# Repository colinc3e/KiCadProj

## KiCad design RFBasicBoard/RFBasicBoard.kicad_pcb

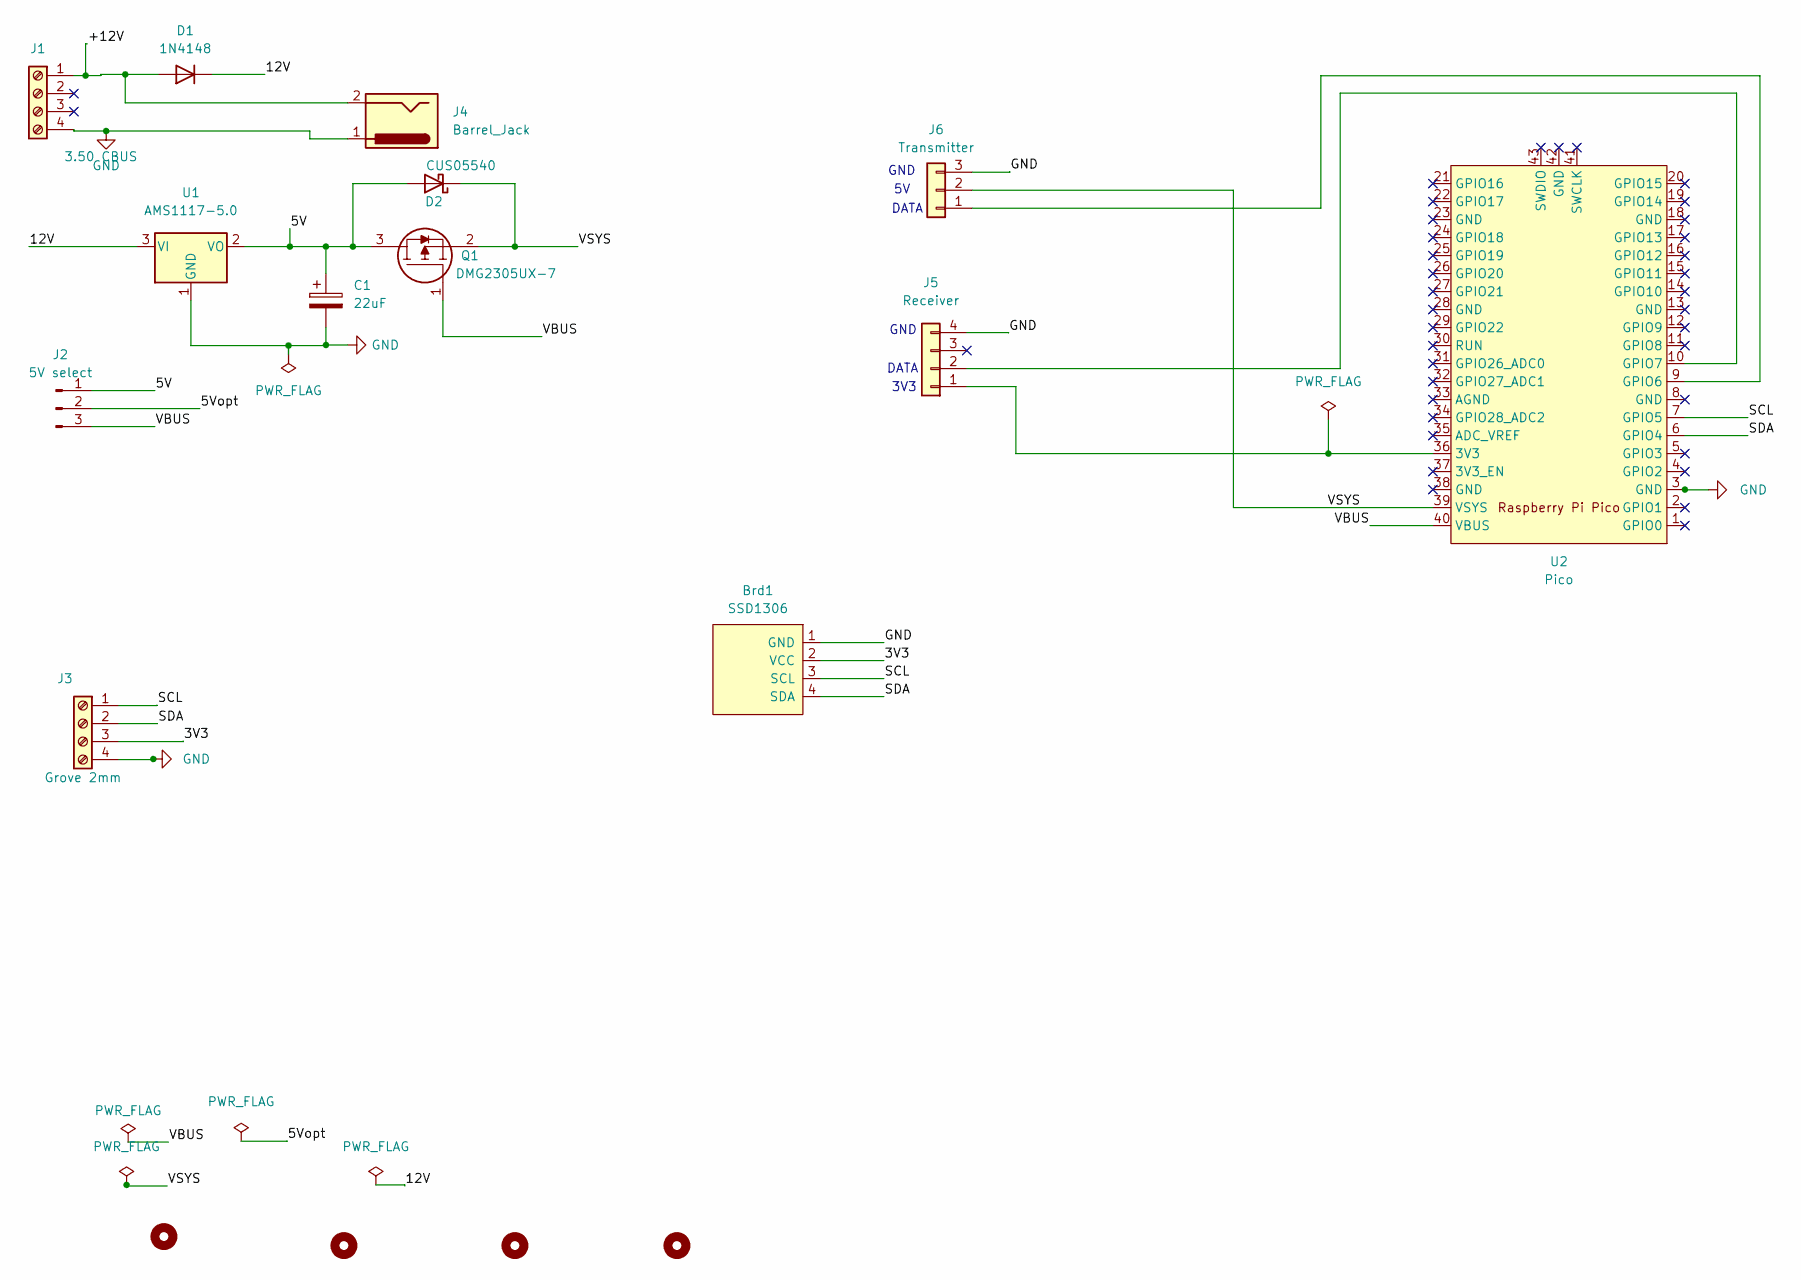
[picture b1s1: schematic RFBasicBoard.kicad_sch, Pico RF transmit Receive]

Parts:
Brd1: SSD1306; 128x64OLED
C1: 22uF; CP_Radial_Tantal_D7.0mm_P5.00mm
D1: 1N4148; D_DO-35_SOD27_P7.62mm_Horizontal
D2: CUS05540; D_SOD-123
H1, H2, H3, H4: MountingHole; MountingHole_3.2mm_M3
J1: 3.50 CBUS; TerminalBlock_Phoenix_PT-1,5-4-3.5-H_1x04_P3.50mm_Horizontal
J2: 5V select; PinHeader_1x03_P2.54mm_Vertical
J3: Grove 2mm; HW4-2.0
J4: Barrel_Jack; BarrelJack_CUI_PJ-102AH_Horizontal
J5: Receiver; PinHeader_1x04_P2.54mm_Vertical
J6: Transmitter; PinHeader_1x03_P2.54mm_Vertical
Q1: DMG2305UX-7; SOT-23; Mouser Part Number 621-DMG2305UX-7
U1: AMS1117-5.0; SOT-223-3_TabPin2
U2: Pico; RP2040Pico

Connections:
/3V3: Brd1.2 (VCC), J3.3
/5V: C1.1, D2.2 (A), J2.1, Q1.3, U1.2 (VO)
/5Vopt: J2.2
/12V: D1.1 (K), U1.3 (VI)
/+12V: D1.2 (A), J1.1, J4.2
/SCL: Brd1.3 (SCL), J3.1, U2.7 (GPIO5)
/SDA: Brd1.4 (SDA), J3.2, U2.6 (GPIO4)
/VBUS: J2.3, Q1.1, U2.40 (VBUS)
/VSYS: D2.1 (K), J6.2, Q1.2, U2.39 (VSYS)
GND: Brd1.1 (GND), C1.2, J1.4, J3.4, J4.1, J5.4, J6.3, U1.1 (GND), U2.3 (GND)
unnamed: J5.1, U2.36 (3V3)
unnamed: J5.2, U2.10 (GPIO7)
unnamed: J6.1, U2.9 (GPIO6)

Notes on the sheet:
GND
DATA
3V3
DATA

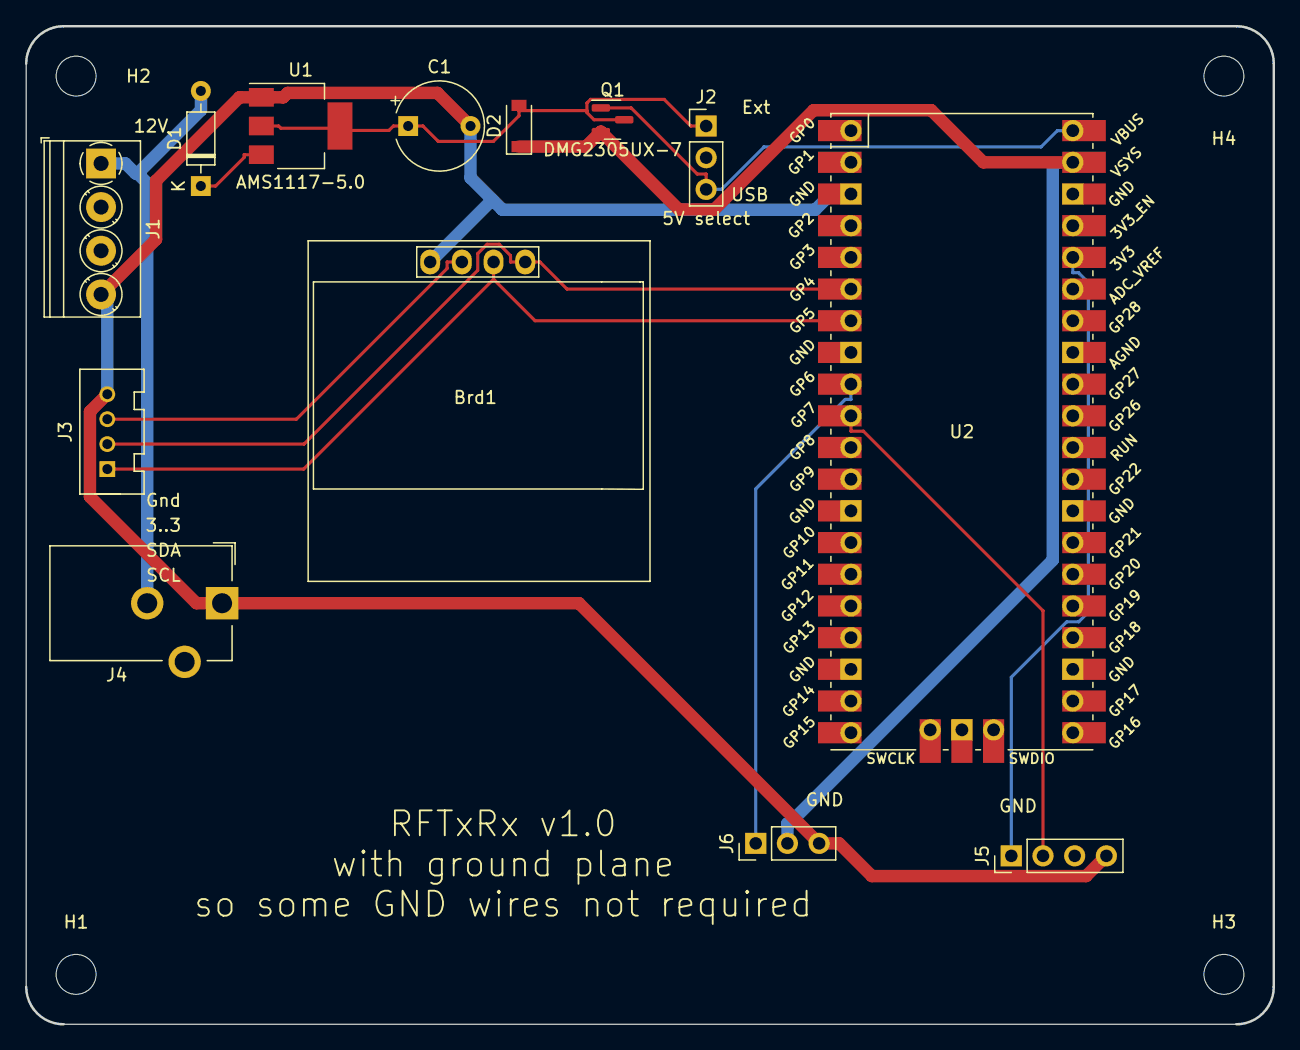
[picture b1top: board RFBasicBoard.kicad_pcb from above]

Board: 2 copper layers, 100.0 x 80.0 mm, 17 parts (0 on the bottom side), 12 nets.

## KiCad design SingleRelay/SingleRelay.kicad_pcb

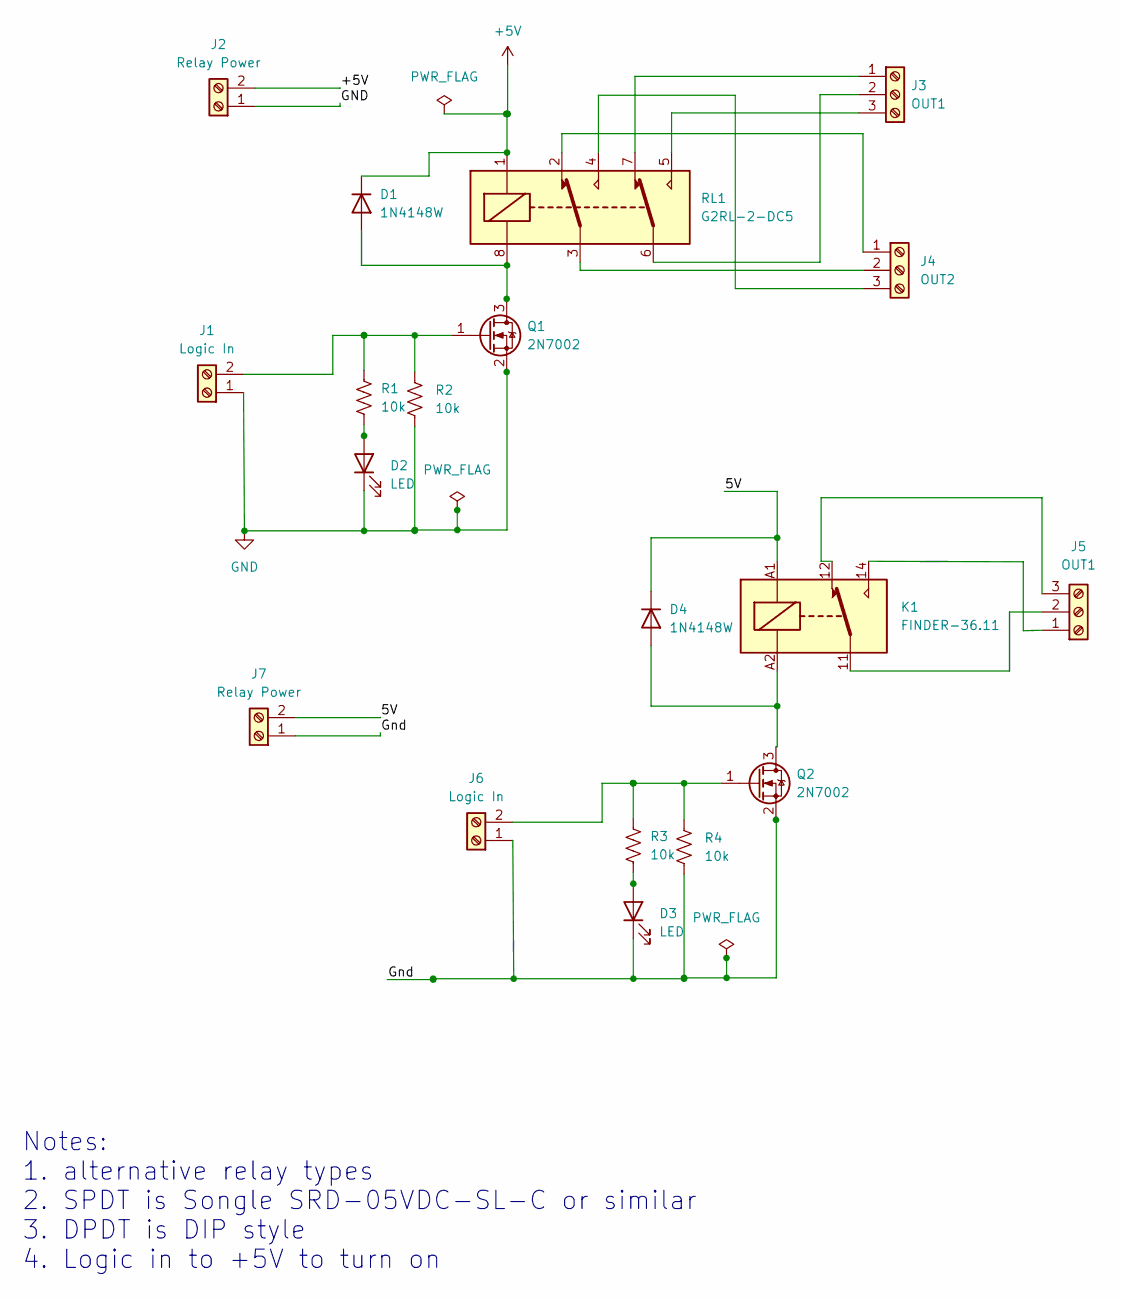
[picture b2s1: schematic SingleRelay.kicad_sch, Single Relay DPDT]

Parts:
D1, D4: 1N4148W; D_SOD-123
D2, D3: LED; LED_D3.0mm_Clear
J1, J6: Logic In; TerminalBlock_Phoenix_PT-1,5-2-3.5-H_1x02_P3.50mm_Horizontal
J2, J7: Relay Power; TerminalBlock_Phoenix_PT-1,5-2-3.5-H_1x02_P3.50mm_Horizontal
J3, J5: OUT1; TerminalBlock_Phoenix_PT-1,5-3-3.5-H_1x03_P3.50mm_Horizontal
J4: OUT2; TerminalBlock_Phoenix_PT-1,5-3-3.5-H_1x03_P3.50mm_Horizontal
K1: FINDER-36.11; Relay_SPDT_Finder_36.11
Q1, Q2: 2N7002; SOT-23
R1, R2, R3, R4: 10k; R_1206_3216Metric
RL1: G2RL-2-DC5; Relay_DPDT_Omron_G2RL

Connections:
+5V: D1.1 (K), J2.2, RL1.1
/5V: D4.1 (K), J7.2, K1.A1
/Gnd: D3.1 (K), J6.1, J7.1, Q2.2 (S), R4.2
GND: D2.1 (K), J1.1, J2.1, Q1.2 (S), R2.2
unnamed: D1.2 (A), Q1.3 (D), RL1.8
unnamed: D2.2 (A), R1.2
unnamed: D3.2 (A), R3.2
unnamed: J1.2, Q1.1 (G), R1.1, R2.1
unnamed: J3.1, RL1.7
unnamed: J3.2, RL1.6
unnamed: J3.3, RL1.5
unnamed: J4.1, RL1.2
unnamed: J4.2, RL1.3
unnamed: J4.3, RL1.4
unnamed: J5.1, K1.14
unnamed: J5.2, K1.11
unnamed: J5.3, K1.12
unnamed: J6.2, Q2.1 (G), R3.1, R4.1
unnamed: D4.2 (A), K1.A2, Q2.3 (D)

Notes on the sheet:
Notes: 1. alternative relay types 2. SPDT is Songle SRD-05VDC-SL-C or similar 3. DPDT is DIP style 4. Logic in to +5V to turn on

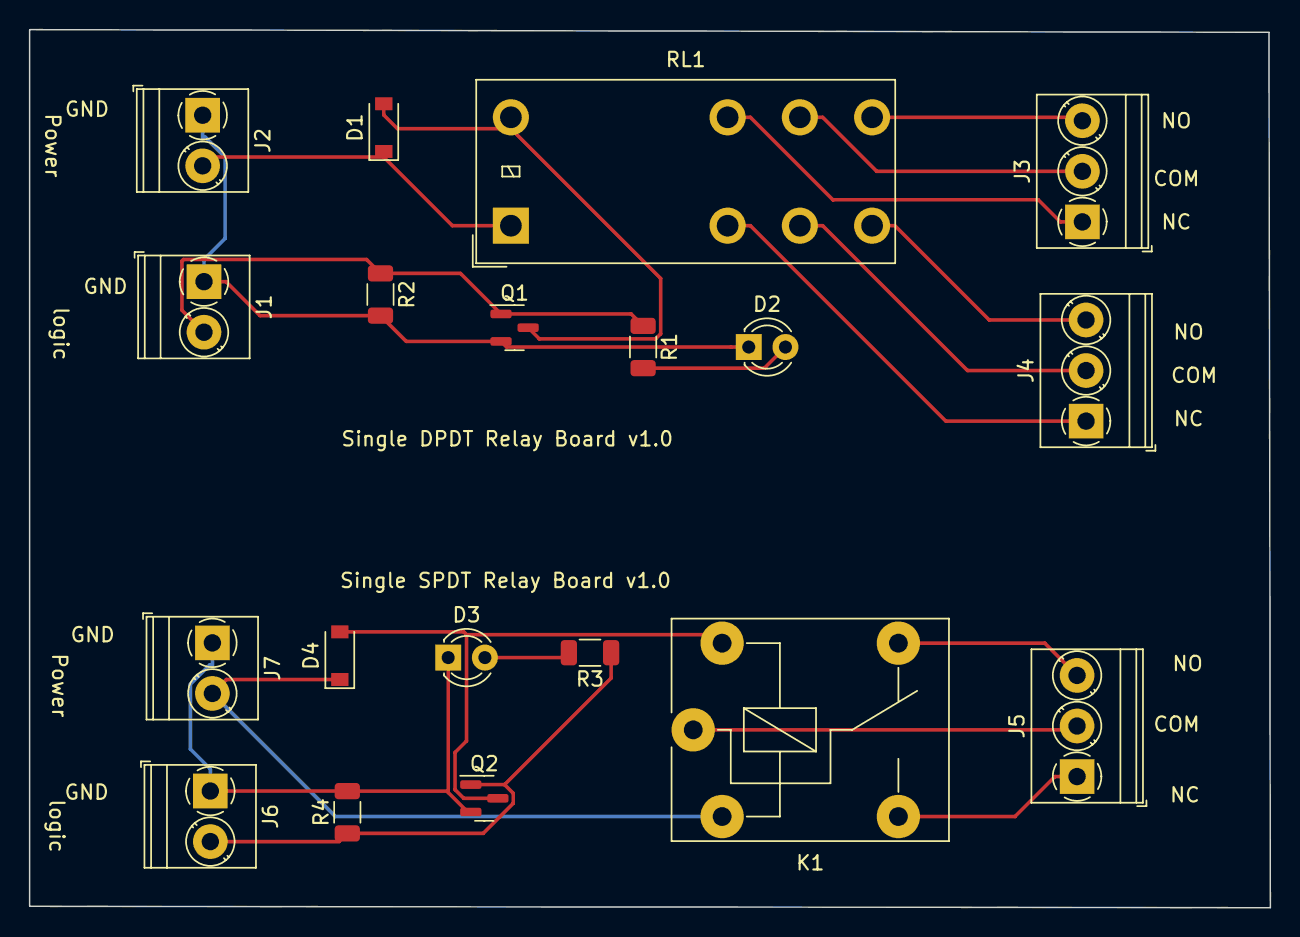
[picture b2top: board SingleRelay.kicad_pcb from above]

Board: 2 copper layers, 85.9 x 60.8 mm, 19 parts (0 on the bottom side), 19 nets.

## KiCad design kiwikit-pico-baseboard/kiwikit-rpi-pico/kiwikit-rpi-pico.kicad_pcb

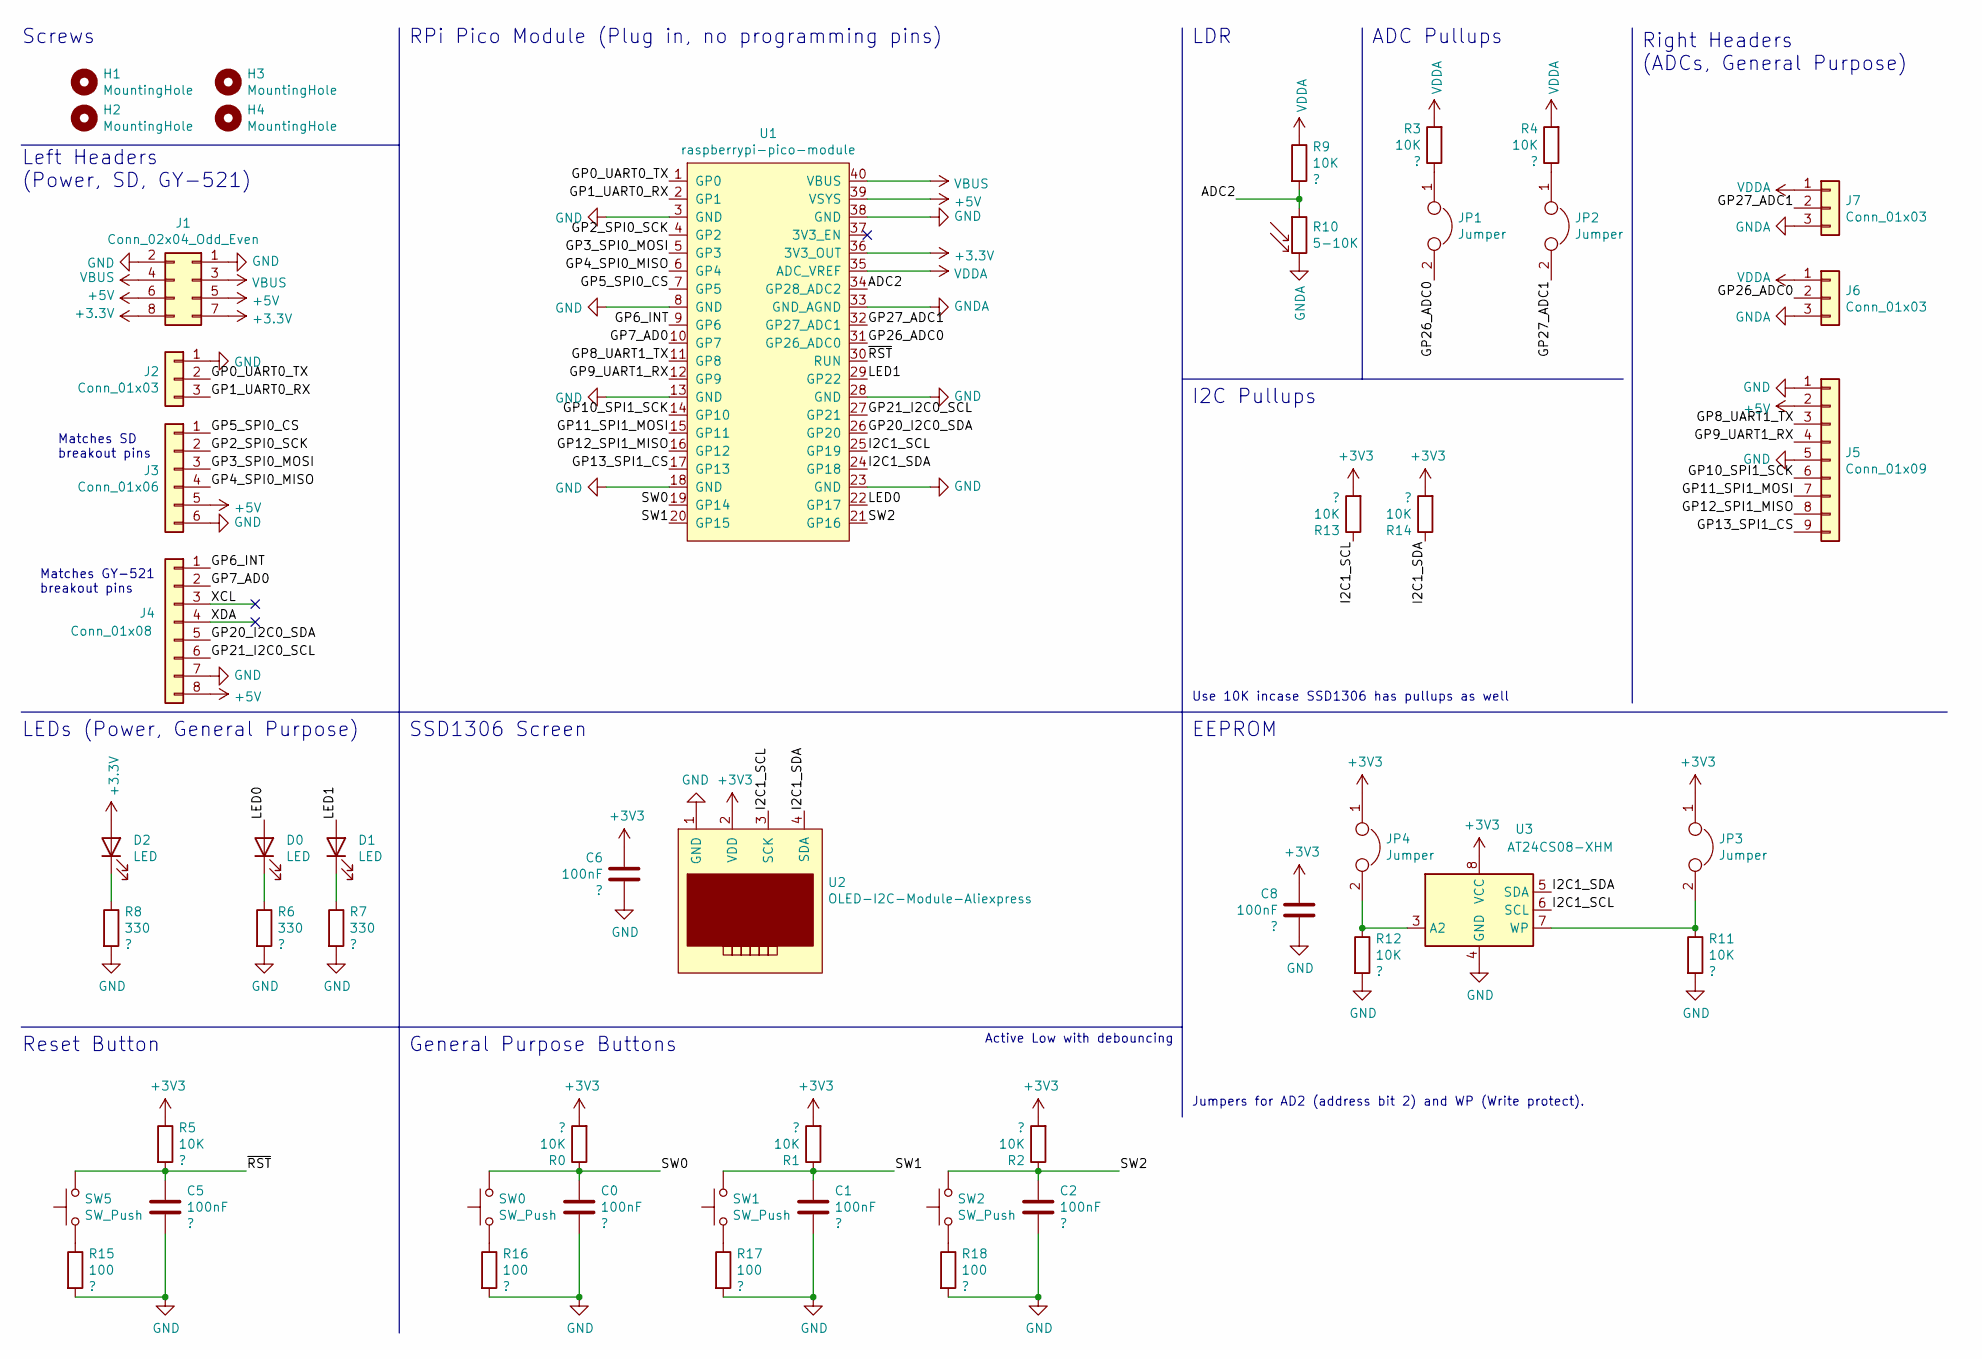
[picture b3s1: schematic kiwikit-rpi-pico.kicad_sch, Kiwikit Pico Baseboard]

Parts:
C0, C1, C2, C5, C6, C8: 100nF; C_Disc_D4.3mm_W1.9mm_P5.00mm
D0, D1, D2: LED; LED_D4.0mm
H1, H2, H3, H4: MountingHole; MountingHole_2.2mm_M2
J1: Conn_02x04_Odd_Even; PinHeader_2x04_P2.54mm_Vertical
J2, J6, J7: Conn_01x03; PinHeader_1x03_P2.54mm_Vertical
J3: Conn_01x06; PinSocket_1x06_P2.54mm_Vertical
J4: Conn_01x08; PinSocket_1x08_P2.54mm_Vertical
J5: Conn_01x09; PinHeader_1x09_P2.54mm_Vertical
JP1, JP2, JP3, JP4: Jumper; PinHeader_1x02_P2.54mm_Vertical
R0, R1, R2, R3, R4, R5, R9, R11, R12, R13, R14: 10K; R_Axial_DIN0207_L6.3mm_D2.5mm_P10.16mm_Horizontal
R6, R7, R8: 330; R_Axial_DIN0207_L6.3mm_D2.5mm_P10.16mm_Horizontal
R10: 5-10K; R_LDR_5.0x4.1mm_P3mm_Vertical
R15, R16, R17, R18: 100; R_Axial_DIN0207_L6.3mm_D2.5mm_P10.16mm_Horizontal
SW0, SW1, SW2: SW_Push; SW_PUSH_6mm_H9.5mm
SW5: SW_Push; SW_PUSH_6mm_H4.3mm
U1: raspberrypi-pico-module
U2: OLED-I2C-Module-Aliexpress
U3: AT24CS08-XHM; DIP-8_W7.62mm

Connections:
+5V: J1.5, J1.6, J3.5, J4.8, J5.2, U1.39 (VSYS)
/ADC2: R9.2, R10.1, U1.34 (GP28_ADC2)
/GP0_UART0_TX: J2.2, U1.1 (GP0)
/GP1_UART0_RX: J2.3, U1.2 (GP1)
/GP2_SPI0_SCK: J3.2, U1.4 (GP2)
/GP3_SPI0_MOSI: J3.3, U1.5 (GP3)
/GP4_SPI0_MISO: J3.4, U1.6 (GP4)
/GP5_SPI0_CS: J3.1, U1.7 (GP5)
/GP6_INT: J4.1, U1.9 (GP6)
/GP7_AD0: J4.2, U1.10 (GP7)
/GP8_UART1_TX: J5.3, U1.11 (GP8)
/GP9_UART1_RX: J5.4, U1.12 (GP9)
/GP10_SPI1_SCK: J5.6, U1.14 (GP10)
/GP11_SPI1_MOSI: J5.7, U1.15 (GP11)
/GP12_SPI1_MISO: J5.8, U1.16 (GP12)
/GP13_SPI1_CS: J5.9, U1.17 (GP13)
/GP20_I2C0_SDA: J4.5, U1.26 (GP20)
/GP21_I2C0_SCL: J4.6, U1.27 (GP21)
/GP26_ADC0: J6.2, JP1.2, U1.31 (GP26_ADC0)
/GP27_ADC1: J7.2, JP2.2, U1.32 (GP27_ADC1)
/I2C1_SCL: R13.1, U1.25 (GP19), U2.3 (SCK), U3.6 (SCL)
/I2C1_SDA: R14.1, U1.24 (GP18), U2.4 (SDA), U3.5 (SDA)
/LED0: D0.2 (A), U1.22 (GP17)
/LED1: D1.2 (A), U1.29 (GP22)
/SW0: C0.2, R0.1, SW0.2, U1.19 (GP14)
/SW1: C1.2, R1.1, SW1.2, U1.20 (GP15)
/SW2: C2.2, R2.1, SW2.2, U1.21 (GP16)
/XCL: J4.3
/XDA: J4.4
/~RST: C5.2, R5.2, SW5.2, U1.30 (RUN)
GND: C0.1, C1.1, C2.1, C5.1, C6.2, C8.2, J1.1, J1.2, J2.1, J3.6, J4.7, J5.1, J5.5, R6.2, R7.2, R8.2, R11.2, R12.2, R15.2, R16.2, R17.2, R18.2, U1.3 (GND), U1.8 (GND), U1.13 (GND), U1.18 (GND), U1.23 (GND), U1.28 (GND), U1.38 (GND), U2.1 (GND), U3.4 (GND)
GNDA: J6.3, J7.3, R10.2, U1.33 (GND_AGND)
unnamed: D0.1 (K), R6.1
unnamed: D1.1 (K), R7.1
unnamed: D2.1 (K), R8.1
unnamed: JP1.1, R3.1
unnamed: JP2.1, R4.1
unnamed: JP3.2, R11.1, U3.7 (WP)
unnamed: JP4.2, R12.1, U3.3 (A2)
unnamed: R15.1, SW5.1
unnamed: R16.1, SW0.1
unnamed: R17.1, SW1.1
unnamed: R18.1, SW2.1
VBUS: J1.3, J1.4, U1.40 (VBUS)
VDDA: J6.1, J7.1, R3.2, R4.2, R9.1, U1.35 (ADC_VREF)

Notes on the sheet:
Screws
LEDs (Power, General Purpose)
SSD1306 Screen
Left Headers (Power, SD, GY-521)
I2C Pullups
Matches SD breakout pins
Active Low with debouncing
RPi Pico Module (Plug in, no programming pins)
Matches GY-521 breakout pins
Right Headers (ADCs, General Purpose)
Use 10K incase SSD1306 has pullups as well
EEPROM
LDR
ADC Pullups
Reset Button
Jumpers for AD2 (address bit 2) and WP (Write protect).
General Purpose Buttons

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
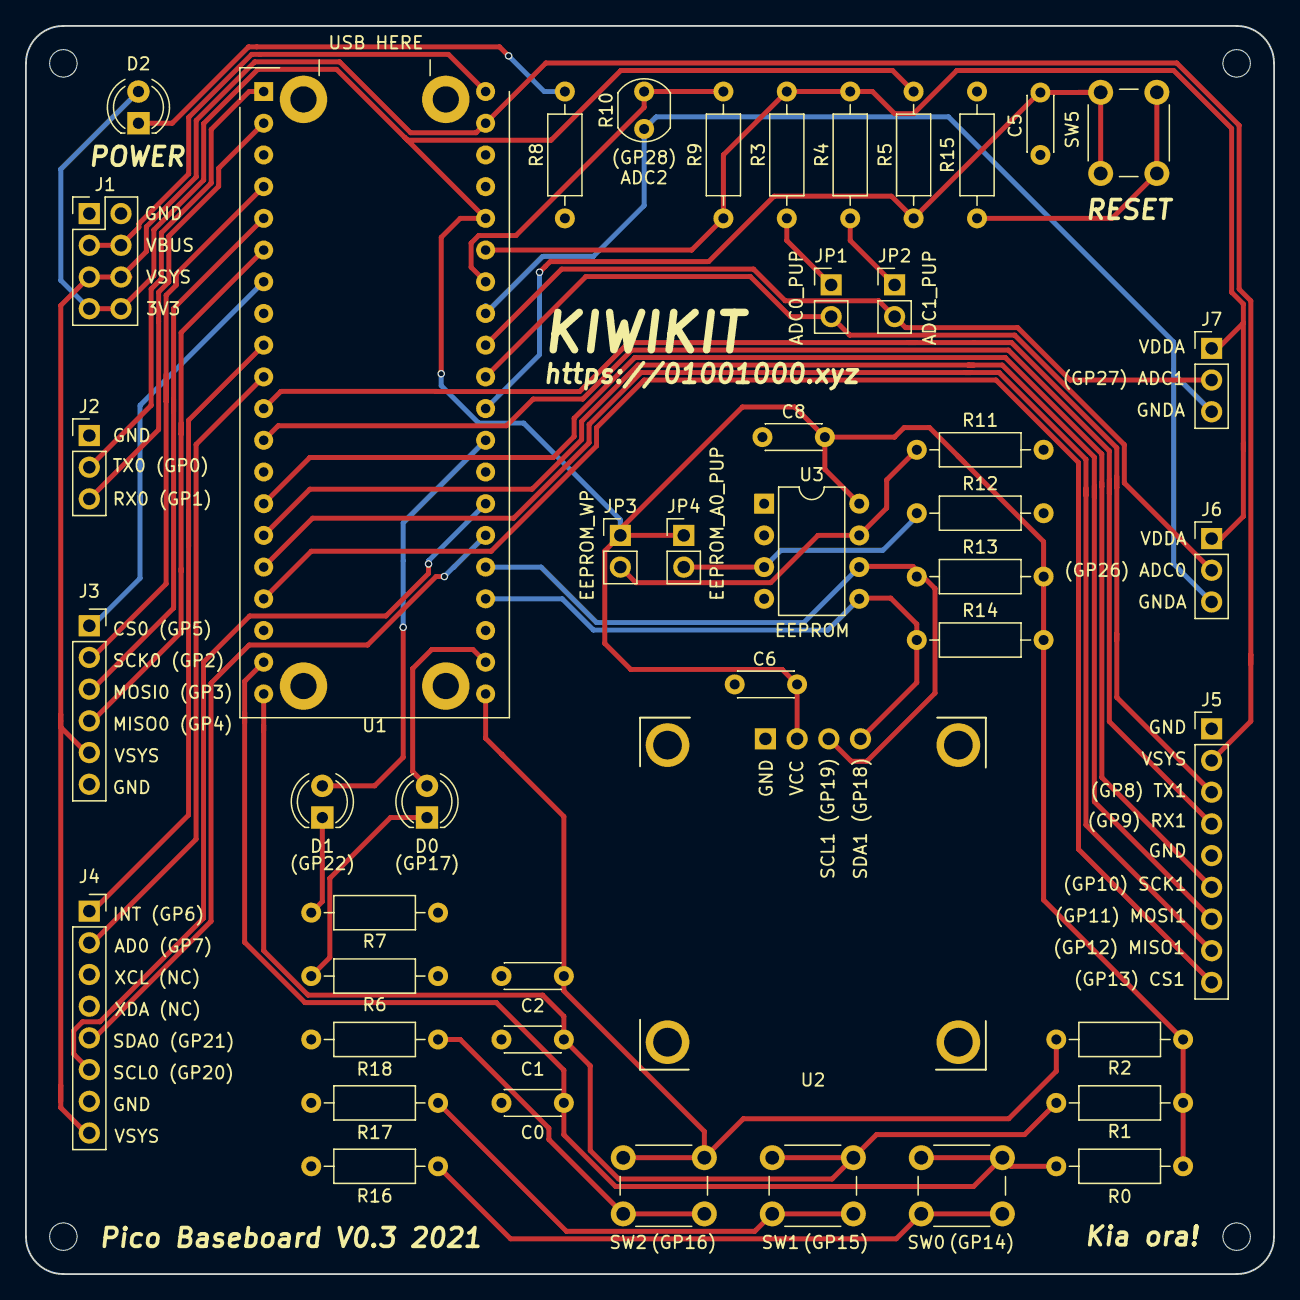
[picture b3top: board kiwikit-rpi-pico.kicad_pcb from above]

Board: 2 copper layers, 100.0 x 100.0 mm, 50 parts (0 on the bottom side), 44 nets.

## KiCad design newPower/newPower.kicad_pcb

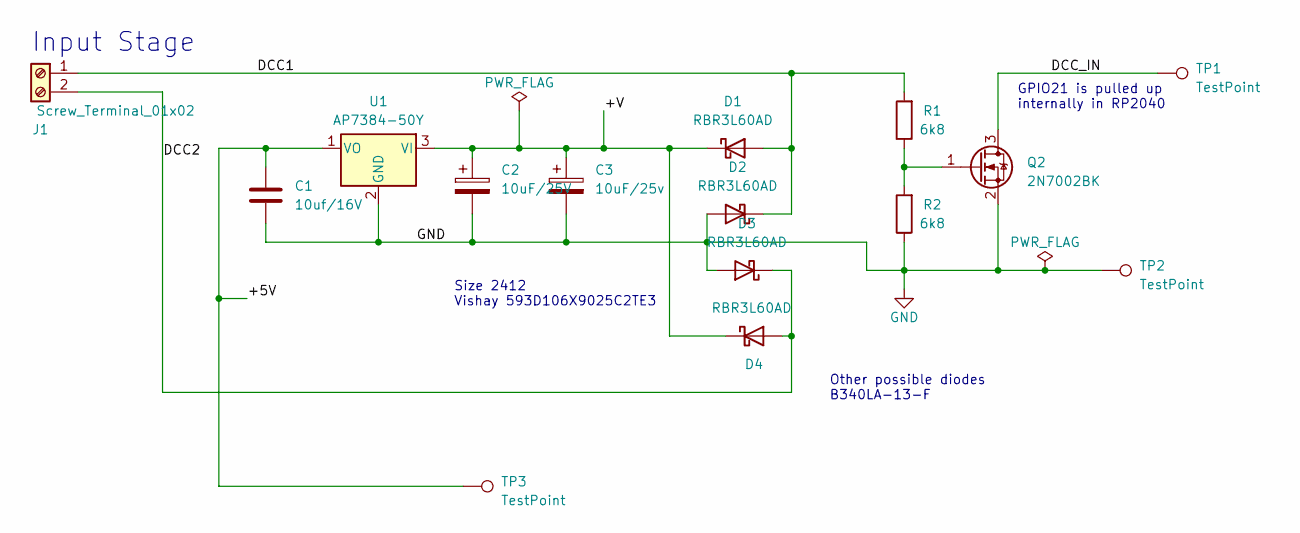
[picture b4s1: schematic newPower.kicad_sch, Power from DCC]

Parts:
C1: 10uf/16V; C_1206_3216Metric_Pad1.33x1.80mm_HandSolder
C2: 10uF/25V; CP_EIA-6032-20_AVX-F_Pad2.25x2.35mm_HandSolder
C3: 10uF/25v; CP_EIA-6032-20_AVX-F_Pad2.25x2.35mm_HandSolder
D1, D2, D3, D4: RBR3L60AD; D_SMA_Handsoldering
J1: Screw_Terminal_01x02; TerminalBlock_Phoenix_PT-1,5-2-3.5-H_1x02_P3.50mm_Horizontal
Q2: 2N7002BK; SOT-23_Handsoldering
R1, R2: 6k8; R_0805_2012Metric_Pad1.20x1.40mm_HandSolder
TP1, TP2, TP3: TestPoint; TestPoint_Pad_2.5x2.5mm
U1: AP7384-50Y; SOT-89-3

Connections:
/+5V: C1.1, TP3.1, U1.1 (VO)
/+V: C2.1, C3.1, D1.1 (K), D4.1 (K), U1.3 (VI)
/DCC1: D1.2 (A), D2.1 (K), J1.1, R1.2
/DCC2: D3.1 (K), D4.2 (A), J1.2
/DCC_IN: TP1.1; also elsewhere on the board
GND: C1.2, C2.2, C3.2, D2.2 (A), D3.2 (A), R2.1, TP2.1, U1.2 (GND); also elsewhere on the board
unnamed 6: R1.1, R2.2; also elsewhere on the board

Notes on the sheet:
Size 2412 Vishay 593D106X9025C2TE3
GPIO21 is pulled up internally in RP2040
Other possible diodes B340LA-13-F
Input Stage

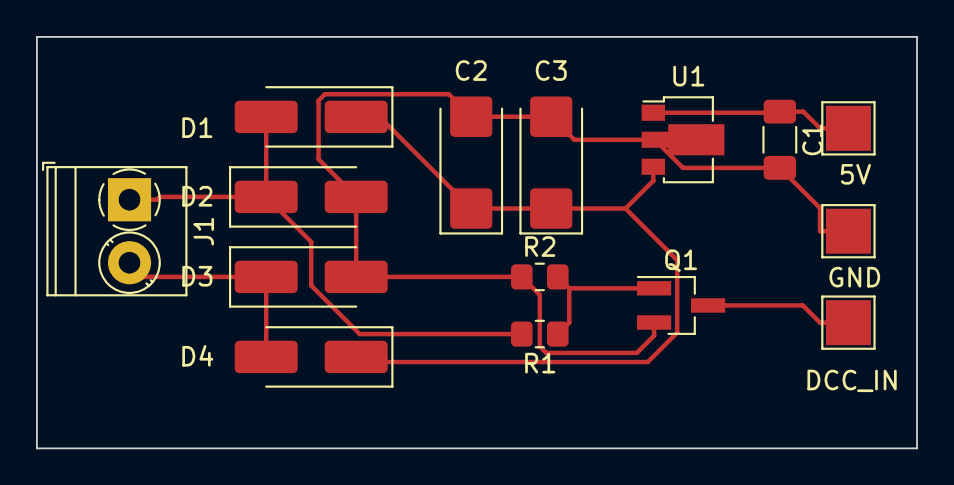
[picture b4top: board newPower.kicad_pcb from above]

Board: 2 copper layers, 48.9 x 22.9 mm, 15 parts (0 on the bottom side), 7 nets.

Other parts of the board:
Q1: 2N7002BK; SOT-23_Handsoldering

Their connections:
/DCC_IN: Q1.3 (D); also elsewhere on the board
GND: Q1.2 (S); also elsewhere on the board
unnamed 6: Q1.1 (G); also elsewhere on the board
